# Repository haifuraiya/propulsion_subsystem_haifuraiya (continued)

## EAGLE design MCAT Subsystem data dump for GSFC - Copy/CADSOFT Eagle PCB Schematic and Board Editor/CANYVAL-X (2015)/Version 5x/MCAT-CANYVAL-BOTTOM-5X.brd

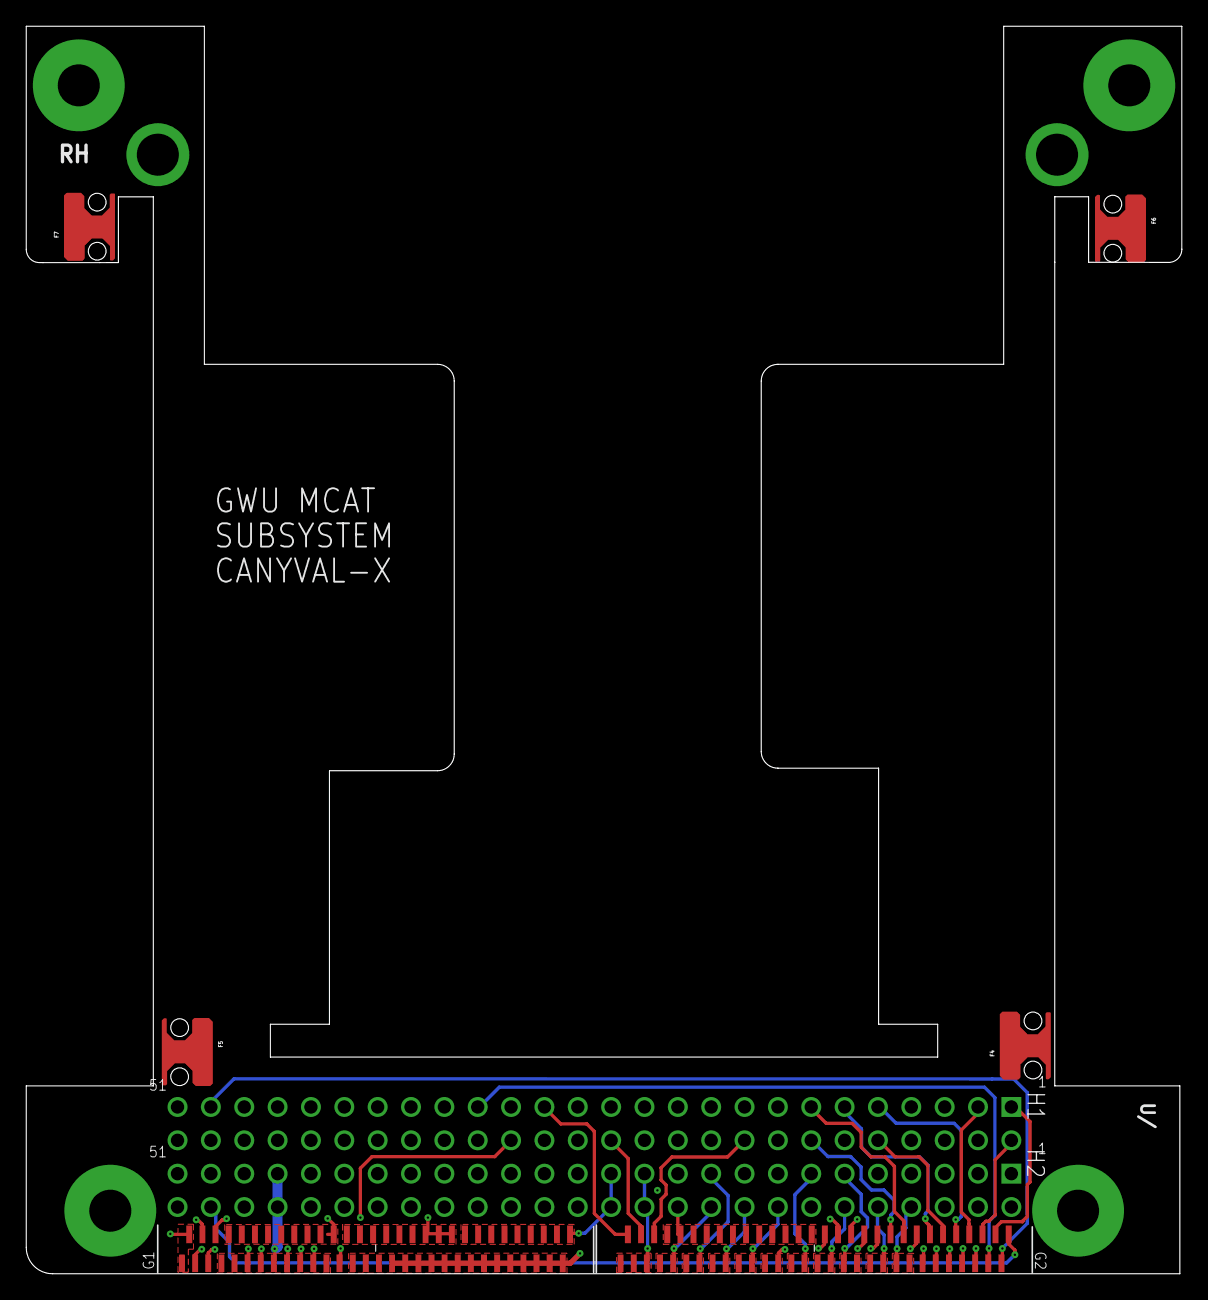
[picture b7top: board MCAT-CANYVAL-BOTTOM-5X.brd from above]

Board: 6 copper layers, 88.0 x 95.0 mm, 9 parts (0 on the bottom side), 45 nets.

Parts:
B1: MCAT-4CU-C-PCB/BOTTOM; MCAT-4CU-C-BOTTOM-V4-BLANK
F4, F5, F6, F7: SMTRAM2-6-5; SMTRA-M2-6-5
GBUS-TOP1:G1, GBUS-TOP1:G2: HIROSE-FH40-60S-0.5SV
GBUS-TOP1:H1: H1-H5-INBOARD-CSK-BUS-CONN; CONN-2X26X0.1-HDR
GBUS-TOP1:H2: H2-H6-OUTBOARD-CSK-BUS-CONN; CONN-2X26X0.1-HDR

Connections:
GBUS-TOP1:G-H1-1: GBUS-TOP1:G2.59, GBUS-TOP1:H1.1
GBUS-TOP1:G-H1-2: GBUS-TOP1:G2.58, GBUS-TOP1:H1.2
GBUS-TOP1:G-H1-3: GBUS-TOP1:G2.57, GBUS-TOP1:H1.3
GBUS-TOP1:G-H1-9: GBUS-TOP1:G2.56, GBUS-TOP1:H1.9
GBUS-TOP1:G-H1-10: GBUS-TOP1:G2.55, GBUS-TOP1:H1.10
GBUS-TOP1:G-H1-11: GBUS-TOP1:G2.54, GBUS-TOP1:H1.11
GBUS-TOP1:G-H1-12: GBUS-TOP1:G2.53, GBUS-TOP1:H1.12
GBUS-TOP1:G-H1-13: GBUS-TOP1:G2.52, GBUS-TOP1:H1.13
GBUS-TOP1:G-H1-14: GBUS-TOP1:G2.51, GBUS-TOP1:H1.14
GBUS-TOP1:G-H1-18: GBUS-TOP1:G2.33, GBUS-TOP1:H1.18
GBUS-TOP1:G-H1-19: GBUS-TOP1:G1.33, GBUS-TOP1:H1.19
GBUS-TOP1:G-H1-20: GBUS-TOP1:G1.32, GBUS-TOP1:H1.20
GBUS-TOP1:G-H1-21: GBUS-TOP1:G2.27, GBUS-TOP1:H1.21
GBUS-TOP1:G-H1-22: GBUS-TOP1:G2.26, GBUS-TOP1:H1.22
GBUS-TOP1:G-H1-23: GBUS-TOP1:G2.25, GBUS-TOP1:H1.23
GBUS-TOP1:G-H1-24: GBUS-TOP1:G2.50, GBUS-TOP1:H1.24
GBUS-TOP1:G-H1-26: GBUS-TOP1:G2.32, GBUS-TOP1:H1.26
GBUS-TOP1:G-H1-29: GBUS-TOP1:G2.31, GBUS-TOP1:H1.29
GBUS-TOP1:G-H1-33: GBUS-TOP1:G2.29, GBUS-TOP1:H1.33
GBUS-TOP1:G-H1-35: GBUS-TOP1:G2.28, GBUS-TOP1:H1.35
GBUS-TOP1:G-H1-45: GBUS-TOP1:G2.47, GBUS-TOP1:H1.45
GBUS-TOP1:G-H1-47: GBUS-TOP1:G2.46, GBUS-TOP1:H1.47
GBUS-TOP1:G-H1-49: GBUS-TOP1:G2.30, GBUS-TOP1:H1.49
GBUS-TOP1:G-H2-50: GBUS-TOP1:G2.60, GBUS-TOP1:H2.50
GBUS-TOP1:M-3V3-BUS: GBUS-TOP1:G1.43, GBUS-TOP1:G1.44, GBUS-TOP1:G1.45, GBUS-TOP1:G1.46, GBUS-TOP1:G1.47, GBUS-TOP1:G1.48, GBUS-TOP1:G1.49, GBUS-TOP1:G1.50, GBUS-TOP1:G1.51, GBUS-TOP1:H2.27, GBUS-TOP1:H2.28
GBUS-TOP1:M-5V-BUS: GBUS-TOP1:G1.52, GBUS-TOP1:G1.53, GBUS-TOP1:G1.54, GBUS-TOP1:G1.55, GBUS-TOP1:G1.56, GBUS-TOP1:G1.57, GBUS-TOP1:G1.58, GBUS-TOP1:G1.59, GBUS-TOP1:G1.60, GBUS-TOP1:H2.25, GBUS-TOP1:H2.26
GBUS-TOP1:M-5V-USB-CHG: GBUS-TOP1:G1.13, GBUS-TOP1:H1.32
GBUS-TOP1:M-12V-BUS: GBUS-TOP1:G2.1, GBUS-TOP1:G2.2, GBUS-TOP1:G2.3, GBUS-TOP1:H2.23, GBUS-TOP1:H2.24
GBUS-TOP1:M-BATV-BUS: GBUS-TOP1:G1.4, GBUS-TOP1:G1.5, GBUS-TOP1:G1.6, GBUS-TOP1:G1.7, GBUS-TOP1:G1.8, GBUS-TOP1:G1.9, GBUS-TOP1:G1.10, GBUS-TOP1:G1.11, GBUS-TOP1:G1.12, GBUS-TOP1:H2.45, GBUS-TOP1:H2.46
GBUS-TOP1:M-SW1-12V: GBUS-TOP1:G2.22, GBUS-TOP1:G2.23, GBUS-TOP1:H2.8
GBUS-TOP1:M-SW2-12V: GBUS-TOP1:G2.20, GBUS-TOP1:G2.21, GBUS-TOP1:H2.10
GBUS-TOP1:M-SW3-BAT: GBUS-TOP1:G2.18, GBUS-TOP1:G2.19, GBUS-TOP1:H2.11
GBUS-TOP1:M-SW4-BAT: GBUS-TOP1:G2.16, GBUS-TOP1:G2.17, GBUS-TOP1:H2.12
GBUS-TOP1:M-SW5-5V: GBUS-TOP1:G2.14, GBUS-TOP1:G2.15, GBUS-TOP1:H2.13
GBUS-TOP1:M-SW6-5V: GBUS-TOP1:G2.12, GBUS-TOP1:G2.13, GBUS-TOP1:H2.15
GBUS-TOP1:M-SW7-5V: GBUS-TOP1:G2.10, GBUS-TOP1:G2.11, GBUS-TOP1:H2.16
GBUS-TOP1:M-SW8-3V3: GBUS-TOP1:G2.8, GBUS-TOP1:G2.9, GBUS-TOP1:H2.18
GBUS-TOP1:M-SW9-3V3: GBUS-TOP1:G2.6, GBUS-TOP1:G2.7, GBUS-TOP1:H2.19
GBUS-TOP1:M-SW10-3V3: GBUS-TOP1:G2.4, GBUS-TOP1:G2.5, GBUS-TOP1:H2.20
GBUS-TOP1:RBF_SW: GBUS-TOP1:G1.1, GBUS-TOP1:G1.31, GBUS-TOP1:H2.37, GBUS-TOP1:H2.38
GBUS-TOP1:SCLIN: GBUS-TOP1:G2.48, GBUS-TOP1:H1.43
GBUS-TOP1:SDAIN: GBUS-TOP1:G2.49, GBUS-TOP1:H1.41
GBUS-TOP1:SEP_SW1: GBUS-TOP1:G1.3, GBUS-TOP1:H2.39
GBUS-TOP1:SEP_SW2: GBUS-TOP1:G1.2, GBUS-TOP1:H2.40
GND: B1.GND, B1.GND@1, B1.GND@2, B1.GND@3, B1.GND@4, B1.GND@13, GBUS-TOP1:G1.14, GBUS-TOP1:G1.15, GBUS-TOP1:G1.16, GBUS-TOP1:G1.17, GBUS-TOP1:G1.18, GBUS-TOP1:G1.19, GBUS-TOP1:G1.20, GBUS-TOP1:G1.21, GBUS-TOP1:G1.22, GBUS-TOP1:G1.23, GBUS-TOP1:G1.24, GBUS-TOP1:G1.25, GBUS-TOP1:G1.26, GBUS-TOP1:G1.27, GBUS-TOP1:G1.28, GBUS-TOP1:G1.29, GBUS-TOP1:G1.30, GBUS-TOP1:G1.34, GBUS-TOP1:G1.35, GBUS-TOP1:G1.36, GBUS-TOP1:G1.37, GBUS-TOP1:G1.38, GBUS-TOP1:G1.39, GBUS-TOP1:G1.40, GBUS-TOP1:G1.41, GBUS-TOP1:G1.42, GBUS-TOP1:G2.24, GBUS-TOP1:G2.34, GBUS-TOP1:G2.35, GBUS-TOP1:G2.36, GBUS-TOP1:G2.37, GBUS-TOP1:G2.38, GBUS-TOP1:G2.39, GBUS-TOP1:G2.40, GBUS-TOP1:G2.41, GBUS-TOP1:G2.42, GBUS-TOP1:G2.43, GBUS-TOP1:G2.44, GBUS-TOP1:G2.45, GBUS-TOP1:H2.9, GBUS-TOP1:H2.14, GBUS-TOP1:H2.17, GBUS-TOP1:H2.21, GBUS-TOP1:H2.22, GBUS-TOP1:H2.29, GBUS-TOP1:H2.30, GBUS-TOP1:H2.32, GBUS-TOP1:H2.47, GBUS-TOP1:H2.48

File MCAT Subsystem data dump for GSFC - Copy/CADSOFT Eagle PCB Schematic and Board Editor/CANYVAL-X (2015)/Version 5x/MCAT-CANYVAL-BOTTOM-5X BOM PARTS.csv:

"Part";"Value";"Device";"Package";"Description";"COPYRIGHT";"MF";"MPN";"PCBLABEL";
"B8";"MCAT-4CU-C-PCB/BOTTOM";"MCAT-4CU-C-PCB/BOTTOM";"MCAT-4CU-C-BOTTOM-V4-BLANK";"";"(c) 2015, The George Washington University. All Rights Reserved";"";"";"BOTTOM";
"F4";"SMTRAM2-6-5";"SMTRAM2-6-5";"SMTRA-M2-6-5";"Type SMTRA - ReelFast Surface Mount Right Angle (R'ANGLE) Fastener (Metric)";"";"Penn Engineering";"SMTRAM2-6-5-DT";"";
"F5";"SMTRAM2-6-5";"SMTRAM2-6-5";"SMTRA-M2-6-5";"Type SMTRA - ReelFast Surface Mount Right Angle (R'ANGLE) Fastener (Metric)";"";"Penn Engineering";"SMTRAM2-6-5-DT";"";
"F6";"SMTRAM2-6-5";"SMTRAM2-6-5";"SMTRA-M2-6-5";"Type SMTRA - ReelFast Surface Mount Right Angle (R'ANGLE) Fastener (Metric)";"";"Penn Engineering";"SMTRAM2-6-5-DT";"";
"F7";"SMTRAM2-6-5";"SMTRAM2-6-5";"SMTRA-M2-6-5";"Type SMTRA - ReelFast Surface Mount Right Angle (R'ANGLE) Fastener (Metric)";"";"Penn Engineering";"SMTRAM2-6-5-DT";"";
"GBUS-TOP1:G1";"HIROSE-FH40-60S-0.5SV";"HIROSE-FH40-60S-0.5SV";"HIROSE-FH40-60S-0.5SV";"";"";"HIROSE/HRS";"FH40-60S-0.5SV";"G1";
"GBUS-TOP1:G2";"HIROSE-FH40-60S-0.5SV";"HIROSE-FH40-60S-0.5SV";"HIROSE-FH40-60S-0.5SV";"";"";"HIROSE/HRS";"FH40-60S-0.5SV";"G2";
"GBUS-TOP1:H1";"H1-H5-INBOARD-CSK-BUS-CONN";"H1-H5-INBOARD-CSK-BUS-CONN";"CONN-2X26X0.1-HDR";"H1/H5/Inboard Cubesat Kit Bus Connector";"";"SAMTEC";"ESQ-126-37-G-D";"H1";
"GBUS-TOP1:H2";"H2-H6-OUTBOARD-CSK-BUS-CONN";"H2-H6-OUTBOARD-CSK-BUS-CONN";"CONN-2X26X0.1-HDR";"";"";"SAMTEC";"ESQ-126-37-G-D";"H2";

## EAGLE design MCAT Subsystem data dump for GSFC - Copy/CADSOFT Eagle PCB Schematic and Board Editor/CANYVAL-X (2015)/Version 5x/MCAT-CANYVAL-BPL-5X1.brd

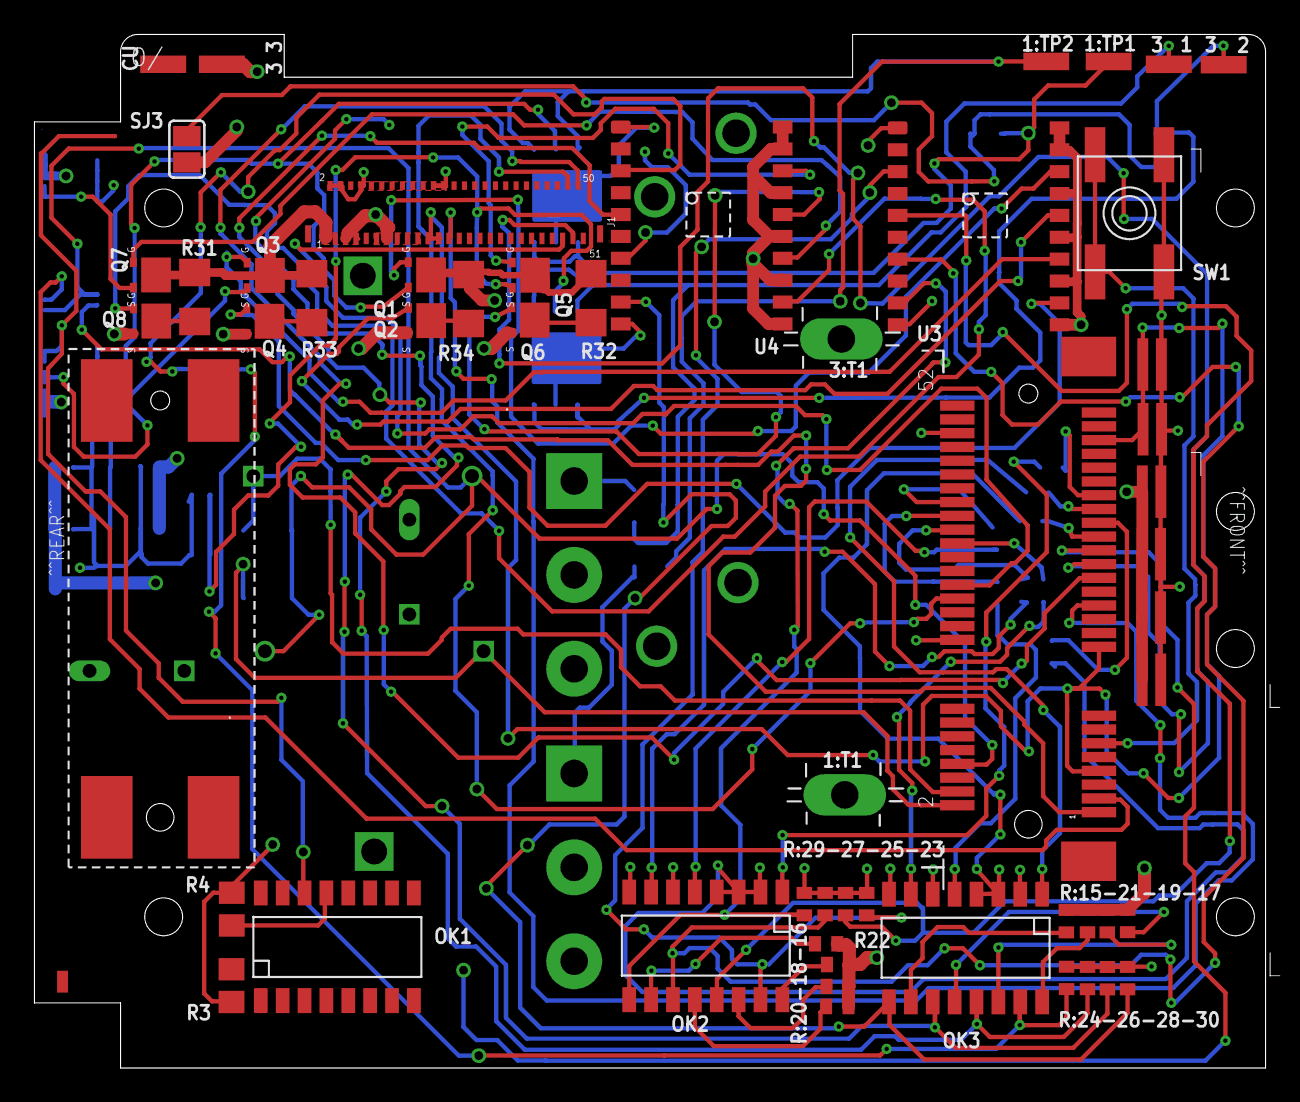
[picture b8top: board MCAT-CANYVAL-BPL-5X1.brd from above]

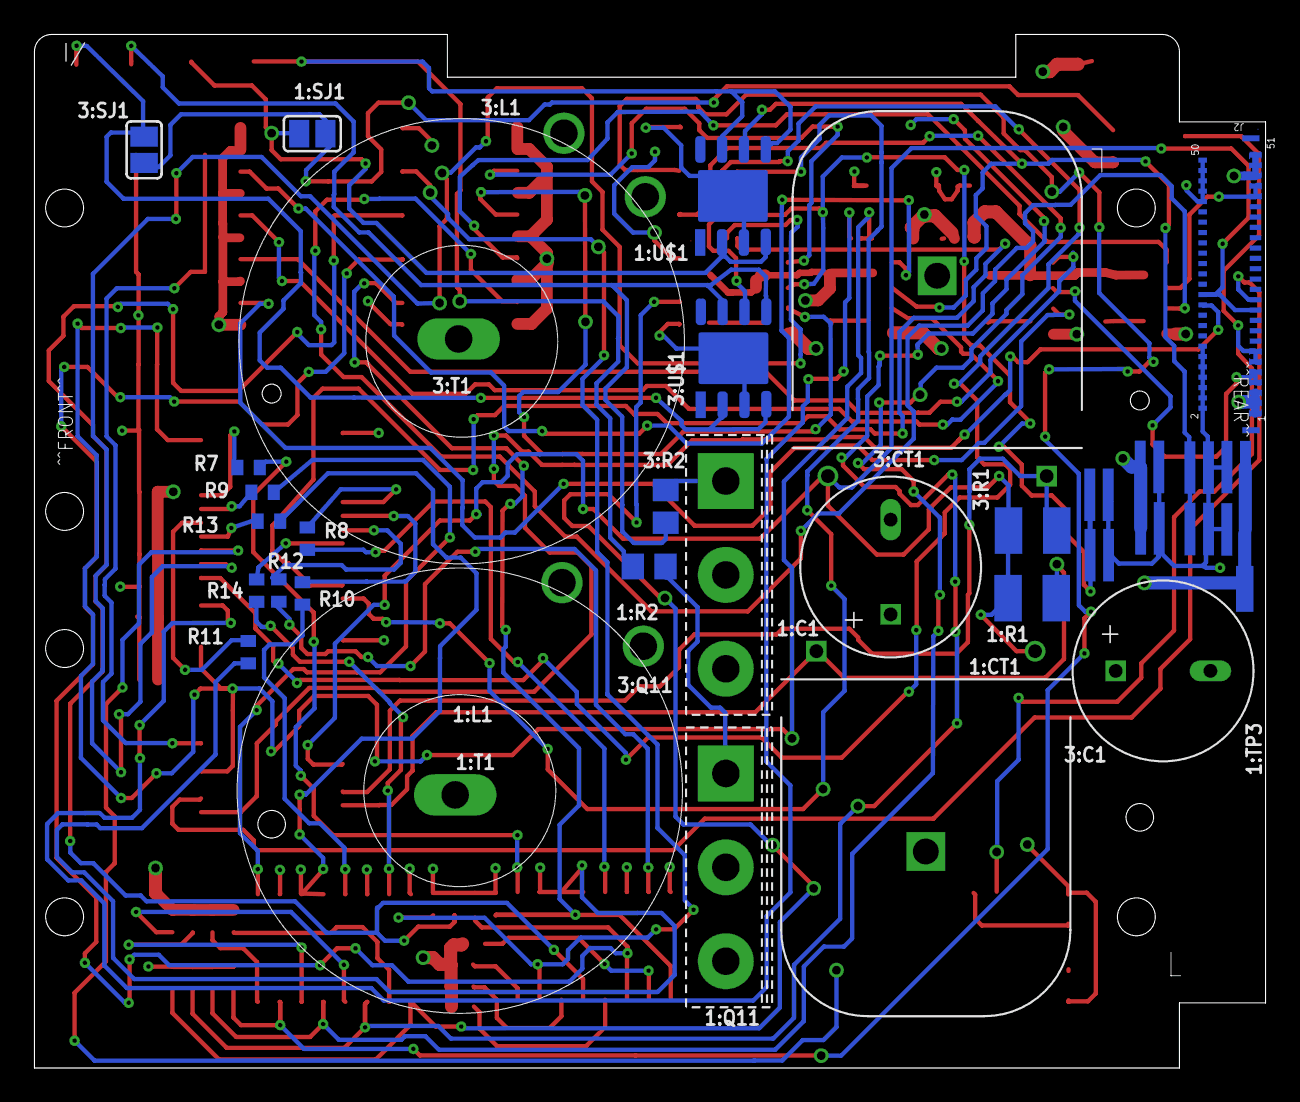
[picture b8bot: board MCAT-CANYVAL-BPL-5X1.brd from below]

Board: 6 copper layers, 71.5 x 60.0 mm, 95 parts (34 on the bottom side), 78 nets.

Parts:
B2: MCAT-4CU-C-PCB/BPL; MCAT-4CU-C-BPL-V4-BLANK
CU-V2L1-1:BC3: BYPASS-CAP-1UF; 0612-REV
CU-V2L1-1:BC4: BYPASS-CAP-0.1UF; 0612-REV
CU-V2L1-1:J7: LATCH_NANO54415_MODULE; LATCH_SD-48099-400
CU-V2L1-1:J9: CONN_NANO54415_MODULE; CONN_SD-67910-001
CU-V2L1-1:OK1: PS2801C-4; SSOP(16PIN)
CU-V2L1-1:R3: 560R; R0805
CU-V2L1-1:R4: 1K2; R0805
CU-V2L1-1:SJ3: 0R; SJ
CU-V2L1-1:SW1: SPST_TACT-EVQQ2; EVQ-Q2
CU-V2L1-1:TP1: PCB-MINI-SMD-TESTPOINT/SQ; PCB-MINI-SMD-TESTPOINT
F1, F2, F3, F4, F5, F6: SMTRAM2-6-5-RA; SMTRA-M2-6-5-RA
J1, J2: MOLEX-502598-5193
PD-V2L1-1:BC1, PD-V2L1-1:BC4: BYPASS-CAP-0.1UF; 0612-REV
PD-V2L1-1:BC2, PD-V2L1-1:BC3: BYPASS-CAP-1UF; 0612-REV
PD-V2L1-1:OK2, PD-V2L1-1:OK3: PS2801C-4; SSOP(16PIN)
PD-V2L1-1:Q1, PD-V2L1-1:Q2, PD-V2L1-1:Q3, PD-V2L1-1:Q4, PD-V2L1-1:Q5, PD-V2L1-1:Q6, PD-V2L1-1:Q7, PD-V2L1-1:Q8: SI5404BDC; 1206-8-CHIPFET
PD-V2L1-1:R7, PD-V2L1-1:R8, PD-V2L1-1:R9, PD-V2L1-1:R10, PD-V2L1-1:R11, PD-V2L1-1:R12, PD-V2L1-1:R13: 5K42; R0402
PD-V2L1-1:R14: 5K42%; R0402
PD-V2L1-1:R15, PD-V2L1-1:R16, PD-V2L1-1:R17, PD-V2L1-1:R18, PD-V2L1-1:R19, PD-V2L1-1:R20, PD-V2L1-1:R21, PD-V2L1-1:R22: 100k; R0402
PD-V2L1-1:R23, PD-V2L1-1:R24, PD-V2L1-1:R25, PD-V2L1-1:R26, PD-V2L1-1:R27, PD-V2L1-1:R28, PD-V2L1-1:R29, PD-V2L1-1:R30: 51k; R0402
PD-V2L1-1:R31, PD-V2L1-1:R32, PD-V2L1-1:R33, PD-V2L1-1:R34: 0.1R; R1206
PD-V2L1-1:U3, PD-V2L1-1:U4: LT1161ISW; 20-LEAD-PLASTIC-SO
PPU-V8C1-1:BC1, PPU-V8C1-1:BC3, PPU-V8C1-3:BC1, PPU-V8C1-3:BC3: BYPASS-CAP-0.1UF; 0612-REV
PPU-V8C1-1:BC2, PPU-V8C1-1:BC4, PPU-V8C1-3:BC2, PPU-V8C1-3:BC4: BYPASS-CAP-1UF; 0612-REV
PPU-V8C1-1:C1, PPU-V8C1-3:C1: 680uF/20WV; CHEMI-CON-PSG-JB5
PPU-V8C1-1:CT1, PPU-V8C1-3:CT1: MURATA-5600-CURR-XFR/RA; MURATA-5600-SERIES-CURR-XFR-RA
PPU-V8C1-1:L1, PPU-V8C1-3:L1: PPUV8-INDUCTOR-V2
PPU-V8C1-1:Q11, PPU-V8C1-3:Q11: IXYH30N120C3D1; IXYS-TO-247-AD-VERT
PPU-V8C1-1:R1, PPU-V8C1-3:R1: 15R; R1210
PPU-V8C1-1:R2, PPU-V8C1-3:R2: 1K; R0805
PPU-V8C1-1:SJ1, PPU-V8C1-3:SJ1: 0R; SJ
PPU-V8C1-1:T1, PPU-V8C1-3:T1: MCAT-SPADE-TERMINAL; SPADE-TERMINAL-FLANGED-NYLON-INSULATED
PPU-V8C1-1:TP1, PPU-V8C1-1:TP2, PPU-V8C1-1:TP3, PPU-V8C1-3:TP1, PPU-V8C1-3:TP2, PPU-V8C1-3:TP3: PCB-MINI-SMD-TESTPOINT/SQ; PCB-MINI-SMD-TESTPOINT
PPU-V8C1-1:U$1, PPU-V8C1-3:U$1: IXDN604/SI; IXYS-SI-8PIN-POWER-SOIC

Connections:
AGND_ADC_GROUND: CU-V2L1-1:J9.8, J2.21, J2.24, PPU-V8C1-1:CT1.3, PPU-V8C1-1:R1.2, PPU-V8C1-3:CT1.3, PPU-V8C1-3:R1.2
CH1_P18H: PD-V2L1-1:Q2.S, PPU-V8C1-1:BC1.1, PPU-V8C1-1:BC2.1, PPU-V8C1-1:C1.POS, PPU-V8C1-1:L1.1, PPU-V8C1-1:TP3.1
CH1_P18L: PD-V2L1-1:Q1.S, PPU-V8C1-1:BC3.1, PPU-V8C1-1:BC4.1, PPU-V8C1-1:U$1.6
CH1_SENSE+: CU-V2L1-1:J9.2, PPU-V8C1-1:CT1.1, PPU-V8C1-1:R1.1
CH2_P18H: J2.1, J2.3, J2.5, PD-V2L1-1:Q4.S
CH2_P18L: J2.7, J2.9, PD-V2L1-1:Q3.S
CH2_SENSE+: CU-V2L1-1:J9.1, J2.22
CH3_P18H: PD-V2L1-1:Q6.S, PPU-V8C1-3:BC1.1, PPU-V8C1-3:BC2.1, PPU-V8C1-3:C1.POS, PPU-V8C1-3:L1.1, PPU-V8C1-3:TP3.1
CH3_P18L: PD-V2L1-1:Q5.S, PPU-V8C1-3:BC3.1, PPU-V8C1-3:BC4.1, PPU-V8C1-3:U$1.6
CH3_SENSE+: CU-V2L1-1:J9.4, PPU-V8C1-3:CT1.1, PPU-V8C1-3:R1.1
CH4_P18H: J2.47, J2.49, J2.51, PD-V2L1-1:Q8.S
CH4_P18L: J2.43, J2.45, PD-V2L1-1:Q7.S
CH4_SENSE+: CU-V2L1-1:J9.3, J2.23
CU-V2L1-1:!RSTI: CU-V2L1-1:J9.11, CU-V2L1-1:SW1.A, CU-V2L1-1:SW1.A'
CU-V2L1-1:SW1_TP1_RTN: CU-V2L1-1:OK1.4, CU-V2L1-1:R3.2
CU-V2L1-1:SW_TP1: CU-V2L1-1:J9.31, CU-V2L1-1:OK1.3
CU-V2L1-1:VOUTA_PULLUP: CU-V2L1-1:OK1.14, CU-V2L1-1:SJ3.2
GND: CU-V2L1-1:BC3.2, CU-V2L1-1:BC4.2, CU-V2L1-1:J9.18, CU-V2L1-1:J9.48, CU-V2L1-1:R3.1, CU-V2L1-1:R4.1, CU-V2L1-1:SW1.B, CU-V2L1-1:SW1.B', J1.2, J1.4, J1.8, J1.10, J1.12, J1.14, J1.16, J1.18, J1.20, J1.22, J1.24, J2.2, J2.4, J2.6, J2.8, J2.10, J2.12, J2.14, J2.42, J2.44, J2.46, J2.48, J2.50, PD-V2L1-1:BC1.2, PD-V2L1-1:BC2.2, PD-V2L1-1:BC3.2, PD-V2L1-1:BC4.2, PD-V2L1-1:OK2.2, PD-V2L1-1:OK2.4, PD-V2L1-1:OK2.6, PD-V2L1-1:OK2.8, PD-V2L1-1:OK3.2, PD-V2L1-1:OK3.4, PD-V2L1-1:OK3.6, PD-V2L1-1:OK3.8, PD-V2L1-1:R23.1, PD-V2L1-1:R24.1, PD-V2L1-1:R25.1, PD-V2L1-1:R26.1, PD-V2L1-1:R27.1, PD-V2L1-1:R28.1, PD-V2L1-1:R29.1, PD-V2L1-1:R30.1, PD-V2L1-1:U3.1, PD-V2L1-1:U3.10, PD-V2L1-1:U4.1, PD-V2L1-1:U4.10, PPU-V8C1-1:BC1.2, PPU-V8C1-1:BC2.2, PPU-V8C1-1:BC3.2, PPU-V8C1-1:BC4.2, PPU-V8C1-1:C1.NEG, PPU-V8C1-1:CT1.PPU-K, PPU-V8C1-1:Q11.E, PPU-V8C1-1:U$1.3, PPU-V8C1-1:U$1.9, PPU-V8C1-3:BC1.2, PPU-V8C1-3:BC2.2, PPU-V8C1-3:BC3.2, PPU-V8C1-3:BC4.2, PPU-V8C1-3:C1.NEG, PPU-V8C1-3:CT1.PPU-K, PPU-V8C1-3:Q11.E, PPU-V8C1-3:U$1.3, PPU-V8C1-3:U$1.9
MCAT_SCL: CU-V2L1-1:J9.27, J1.50
MCAT_SDA: CU-V2L1-1:J9.29, J1.49
unnamed: CU-V2L1-1:J9.33, PD-V2L1-1:R13.2
P3: CU-V2L1-1:BC3.1, CU-V2L1-1:BC4.1, CU-V2L1-1:J9.7, CU-V2L1-1:J9.17, CU-V2L1-1:J9.47, J1.21, J1.23
PD-V2L1-1:CH1HG: PD-V2L1-1:Q2.G, PD-V2L1-1:U3.16
PD-V2L1-1:CH1LG: PD-V2L1-1:Q1.G, PD-V2L1-1:U3.18
PD-V2L1-1:CH1S: PD-V2L1-1:Q2.D, PD-V2L1-1:R34.1
PD-V2L1-1:CH2HG: PD-V2L1-1:Q4.G, PD-V2L1-1:U3.12
PD-V2L1-1:CH2LG: PD-V2L1-1:Q3.G, PD-V2L1-1:U3.14
PD-V2L1-1:CH2S: PD-V2L1-1:Q4.D, PD-V2L1-1:R33.1
PD-V2L1-1:CH3HG: PD-V2L1-1:Q6.G, PD-V2L1-1:U4.16
PD-V2L1-1:CH3LG: PD-V2L1-1:Q5.G, PD-V2L1-1:U4.18
PD-V2L1-1:CH3S: PD-V2L1-1:Q6.D, PD-V2L1-1:R32.1
PD-V2L1-1:CH4HG: PD-V2L1-1:Q8.G, PD-V2L1-1:U4.12
PD-V2L1-1:CH4LG: PD-V2L1-1:Q7.G, PD-V2L1-1:U4.14
PD-V2L1-1:CH4S: PD-V2L1-1:Q8.D, PD-V2L1-1:R31.1
PD-V2L1-1:N$4: PD-V2L1-1:OK2.16, PD-V2L1-1:R16.2
PD-V2L1-1:N$5: PD-V2L1-1:OK2.14, PD-V2L1-1:R18.2
PD-V2L1-1:N$7: PD-V2L1-1:OK2.12, PD-V2L1-1:R20.2
PD-V2L1-1:N$9: PD-V2L1-1:OK2.10, PD-V2L1-1:R22.2
PD-V2L1-1:N$10: PD-V2L1-1:OK3.16, PD-V2L1-1:R21.2
PD-V2L1-1:N$11: PD-V2L1-1:OK3.14, PD-V2L1-1:R19.2
PD-V2L1-1:N$12: PD-V2L1-1:OK3.12, PD-V2L1-1:R17.2
PD-V2L1-1:N$13: PD-V2L1-1:OK3.10, PD-V2L1-1:R15.2
PD-V2L1-1:OK1E1: PD-V2L1-1:OK2.15, PD-V2L1-1:R23.2, PD-V2L1-1:U3.3
PD-V2L1-1:OK1E2: PD-V2L1-1:OK2.13, PD-V2L1-1:R25.2, PD-V2L1-1:U3.5
PD-V2L1-1:OK1E3: PD-V2L1-1:OK2.11, PD-V2L1-1:R27.2, PD-V2L1-1:U3.7
PD-V2L1-1:OK1E4: PD-V2L1-1:OK2.9, PD-V2L1-1:R29.2, PD-V2L1-1:U3.9
PD-V2L1-1:OK2E1: PD-V2L1-1:OK3.15, PD-V2L1-1:R24.2, PD-V2L1-1:U4.3
PD-V2L1-1:OK2E2: PD-V2L1-1:OK3.13, PD-V2L1-1:R26.2, PD-V2L1-1:U4.5
PD-V2L1-1:OK2E3: PD-V2L1-1:OK3.11, PD-V2L1-1:R28.2, PD-V2L1-1:U4.7
PD-V2L1-1:OK2E4: PD-V2L1-1:OK3.9, PD-V2L1-1:R30.2, PD-V2L1-1:U4.9
PD-V2L1-1:P18_SW1: PD-V2L1-1:OK2.1, PD-V2L1-1:R7.1
PD-V2L1-1:P18_SW2: PD-V2L1-1:OK2.5, PD-V2L1-1:R8.1
PD-V2L1-1:P18_SW3: PD-V2L1-1:OK3.1, PD-V2L1-1:R9.1
PD-V2L1-1:P18_SW4: PD-V2L1-1:OK3.5, PD-V2L1-1:R10.1
PD-V2L1-1:P18_SW5: PD-V2L1-1:OK2.3, PD-V2L1-1:R11.1
PD-V2L1-1:P18_SW6: PD-V2L1-1:OK2.7, PD-V2L1-1:R12.1
PD-V2L1-1:P18_SW7: PD-V2L1-1:OK3.3, PD-V2L1-1:R13.1
PD-V2L1-1:P18_SW8: PD-V2L1-1:OK3.7, PD-V2L1-1:R14.1
PPU-V8C1-1:N$2: PPU-V8C1-1:Q11.G, PPU-V8C1-1:R2.2
PPU-V8C1-1:PPU-A: PPU-V8C1-1:L1.2, PPU-V8C1-1:Q11.C, PPU-V8C1-1:T1.T
PPU-V8C1-1:TPIPD_IN: PPU-V8C1-1:SJ1.2, PPU-V8C1-1:TP1.1, PPU-V8C1-1:U$1.2, PPU-V8C1-1:U$1.4
PPU-V8C1-1:TPIPD_OUT: PPU-V8C1-1:R2.1, PPU-V8C1-1:TP2.1, PPU-V8C1-1:U$1.5, PPU-V8C1-1:U$1.7
PPU-V8C1-3:N$2: PPU-V8C1-3:Q11.G, PPU-V8C1-3:R2.2
PPU-V8C1-3:PPU-A: PPU-V8C1-3:L1.2, PPU-V8C1-3:Q11.C, PPU-V8C1-3:T1.T
PPU-V8C1-3:TPIPD_IN: PPU-V8C1-3:SJ1.2, PPU-V8C1-3:TP1.1, PPU-V8C1-3:U$1.2, PPU-V8C1-3:U$1.4
PPU-V8C1-3:TPIPD_OUT: PPU-V8C1-3:R2.1, PPU-V8C1-3:TP2.1, PPU-V8C1-3:U$1.5, PPU-V8C1-3:U$1.7
SW_P18H1: CU-V2L1-1:J9.35, PD-V2L1-1:R11.2
SW_P18H3: CU-V2L1-1:J9.34, PD-V2L1-1:R12.2
SW_P18H4: CU-V2L1-1:J9.32, PD-V2L1-1:R14.2
SW_P18L: CU-V2L1-1:J9.39, PD-V2L1-1:R7.2
SW_P18L2: CU-V2L1-1:J9.38, PD-V2L1-1:R8.2
SW_P18L3: CU-V2L1-1:J9.37, PD-V2L1-1:R9.2
SW_P18L4: CU-V2L1-1:J9.36, PD-V2L1-1:R10.2
SW_RUNPMA: CU-V2L1-1:J9.23, J1.25
TP1_OUT: CU-V2L1-1:OK1.13, CU-V2L1-1:R4.2, CU-V2L1-1:TP1.1, J2.11, J2.13, PPU-V8C1-1:SJ1.1, PPU-V8C1-3:SJ1.1
UART0_RX: CU-V2L1-1:J9.24, J1.48
UART0_TX: CU-V2L1-1:J9.26, J1.47
VOUTA: CU-V2L1-1:SJ3.1, J1.1, J1.3, J1.5, J1.7, J1.11, J1.13, J1.15, J1.17, J1.19, PD-V2L1-1:BC1.1, PD-V2L1-1:BC2.1, PD-V2L1-1:BC3.1, PD-V2L1-1:BC4.1, PD-V2L1-1:Q1.D, PD-V2L1-1:Q3.D, PD-V2L1-1:Q5.D, PD-V2L1-1:Q7.D, PD-V2L1-1:R15.1, PD-V2L1-1:R16.1, PD-V2L1-1:R17.1, PD-V2L1-1:R18.1, PD-V2L1-1:R19.1, PD-V2L1-1:R20.1, PD-V2L1-1:R21.1, PD-V2L1-1:R22.1, PD-V2L1-1:R31.2, PD-V2L1-1:R32.2, PD-V2L1-1:R33.2, PD-V2L1-1:R34.2, PD-V2L1-1:U3.11, PD-V2L1-1:U3.13, PD-V2L1-1:U3.15, PD-V2L1-1:U3.17, PD-V2L1-1:U3.19, PD-V2L1-1:U3.20, PD-V2L1-1:U4.11, PD-V2L1-1:U4.13, PD-V2L1-1:U4.15, PD-V2L1-1:U4.17, PD-V2L1-1:U4.19, PD-V2L1-1:U4.20

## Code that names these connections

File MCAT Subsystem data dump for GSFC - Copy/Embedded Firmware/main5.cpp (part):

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	//define GPIO for TESTCU configuration
	cout << "Setting GPIO lines for TESTCU configuration" <<endl;
	//assign TSW_RUNPMA
	SW_RUNPMA.function(PIN_23_GPIO);
	//assign TSW_TP1
	SW_TP1.function(PIN_12_GPIO);

	//assign TSW_P18L12
	SW_P18L12.function(PIN_16_GPIO);
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	cout << "Setting GPIO lines for FLTCU configuration" <<endl;

	//assign SW_RUNPMA
	SW_RUNPMA.function(PIN_23_GPIO);
	//assign SW_TP1
	SW_TP1.function(PIN_31_GPIO);
	//assign SW_P18L1
	SW_P18L1.function(PIN_39_GPIO);
	//assign SW_P18L2
	SW_P18L2.function(PIN_38_GPIO);
	//assign SW_P18L3
	SW_P18L3.function(PIN_37_GPIO);
	//assign SW_P18L4
	SW_P18L4.function(PIN_36_GPIO);
	//assign SW_P18H1
	SW_P18H1.function(PIN_35_GPIO);
	//assign SW_P18H2
	SW_P18H2.function(PIN_34_GPIO);
	//assign SW_P18H3
	SW_P18H3.function(PIN_33_GPIO);
	//assign SW_P18H4
	SW_P18H4.function(PIN_32_GPIO);
#else
#endif
#endif
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
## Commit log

2022-08-25 Update README.md
    initial seed /samudra
    contains 2015 archive of MCAT Subsystem data dump for GSFC - golden cd-rom provided by GWU to NASA GSFC.
2022-08-26 Update README.md
    fixed formatting
2022-08-26 initial archive
    pushing initial archive of 6.3c of MCAT Subsystem data dump for GSFC - Copy
